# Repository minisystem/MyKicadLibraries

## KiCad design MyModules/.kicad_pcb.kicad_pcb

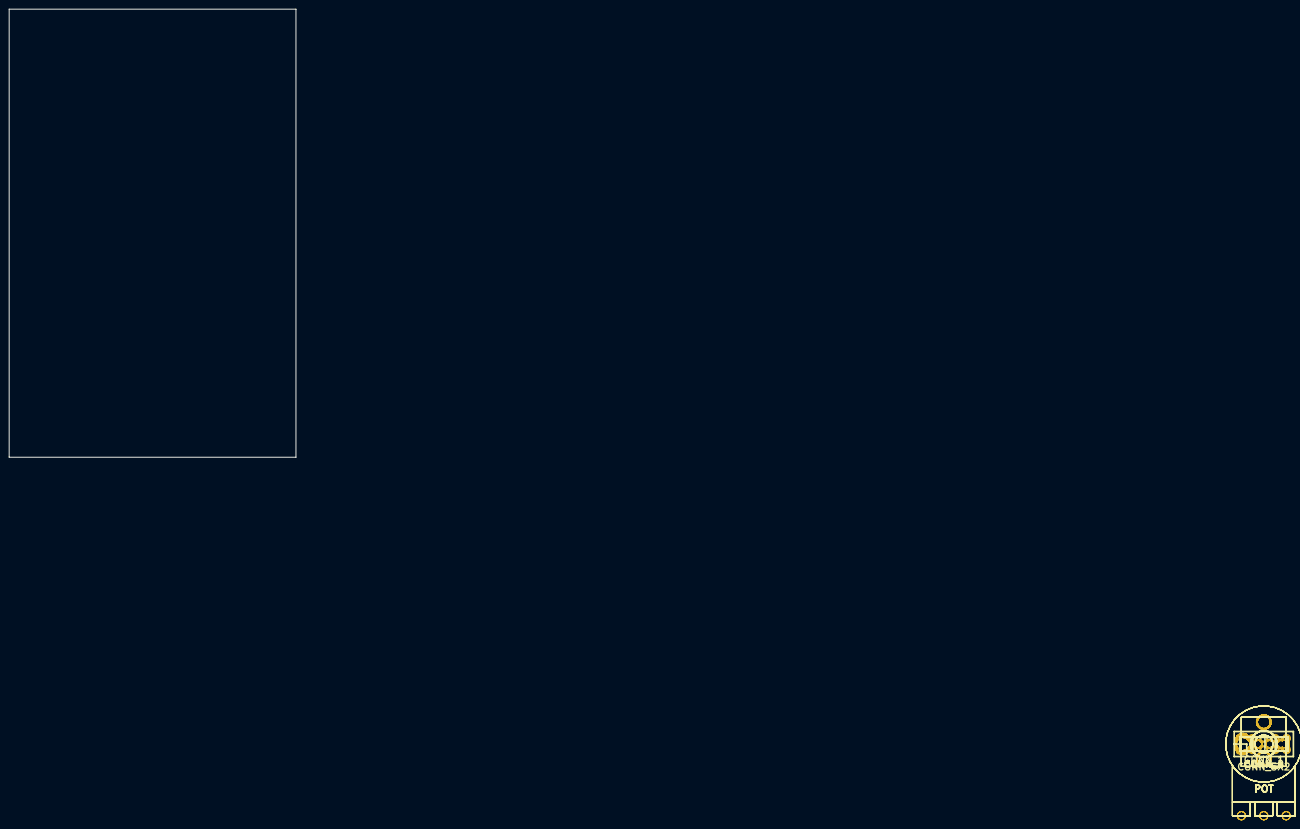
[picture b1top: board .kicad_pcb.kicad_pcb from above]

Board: 2 copper layers, 64.0 x 100.0 mm, 17 parts (0 on the bottom side), 16 nets, no tracks yet.

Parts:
J1, J2, J3, J4, J5, J6: JACK_MONO_SW; PJ-301B-JACK
JP1, JP2, JP4: CONN_4; CONN_0100_X_4
JP3: CONN_2; CONN_0100_X_2
P1: CONN_1; CONN_0100_X_1
P2: CONN_5X2; CONN_0100_2X5_10
RV1, RV2, RV3, RV4, RV5: POT; RV16A-41

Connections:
1V/OCT JACK: J5.1, JP1.1
+12V: JP4.1, P2.1, P2.2
+VCC: P1.1, RV4.3
-12V: JP4.4, P2.9, P2.10
AUDIO IN 2: JP2.3, RV1.2
AUDIO JACK 1: J1.1, JP2.4
AUDIO JACK 2: J2.1, RV1.3
AUDIO OUT JACK: J6.1, JP3.2
CV 1: JP1.3, RV2.2
CV 2: JP1.2, RV3.2
CV JACK 1: J3.1, RV2.3
CV JACK 2: J4.1, RV3.3
FREQ POT W: JP1.4, RV4.2
GND: J1.3, J2.3, J3.3, J4.3, J5.3, J6.3, JP3.1, JP4.2, JP4.3, P2.3, P2.4, P2.5, P2.6, P2.7, P2.8, RV1.1, RV2.1, RV3.1, RV4.1, RV5.1
RES POT +: JP2.1, RV5.3
RES POT W: JP2.2, RV5.2

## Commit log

2015-01-07 library update
2015-02-14 commit, cleaned up a bit and added some stuff to .gitignore
2015-04-27 updated MySynthParts.lib
2015-05-10 latest update after QuiltSliver and Eurorack JP6 filter PCB updates
2015-12-09 module footprint library update
2016-01-07 January 2016 library update
2016-01-07 updated .gitignore to exclude a couple of .exe scripts
2016-01-07 added MC14584 hex schmitt trigger to schematic library
2016-01-27 January 2016 library updates
2016-03-07 March Library commit
2016-04-29 library update April 2016
2016-07-29 added PMP4201 and 5201 NPN/PNP patched pair schematic symbols
2016-09-16 September library update, added 3D models for 808 parts
2016-12-15 December 2016 library update
2017-05-11 May 2017 library updates
2017-10-16 October 2017 library updats
2018-03-14 Starting the addition of my utility to make finely grained replacements of modules in a KiCad file
2018-03-14 Make the parser-replacer take command line arguments, and give examples
2018-03-14 March 2018 libs
2019-06-04 June 2019 library backup
